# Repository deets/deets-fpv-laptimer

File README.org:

| Pin | Function |
|-----+----------|
|   1 | data     |
|   2 | cs       |
|   3 | clk      |
|   4 | gnd      |
|   5 | vcc      |
|   6 | rssi     |
|   7 | ?        |
|   8 | video    |
|   9 | gnd      |

* Credits

https://github.com/Spacefish/RichWave/blob/master/RichWave.cpp

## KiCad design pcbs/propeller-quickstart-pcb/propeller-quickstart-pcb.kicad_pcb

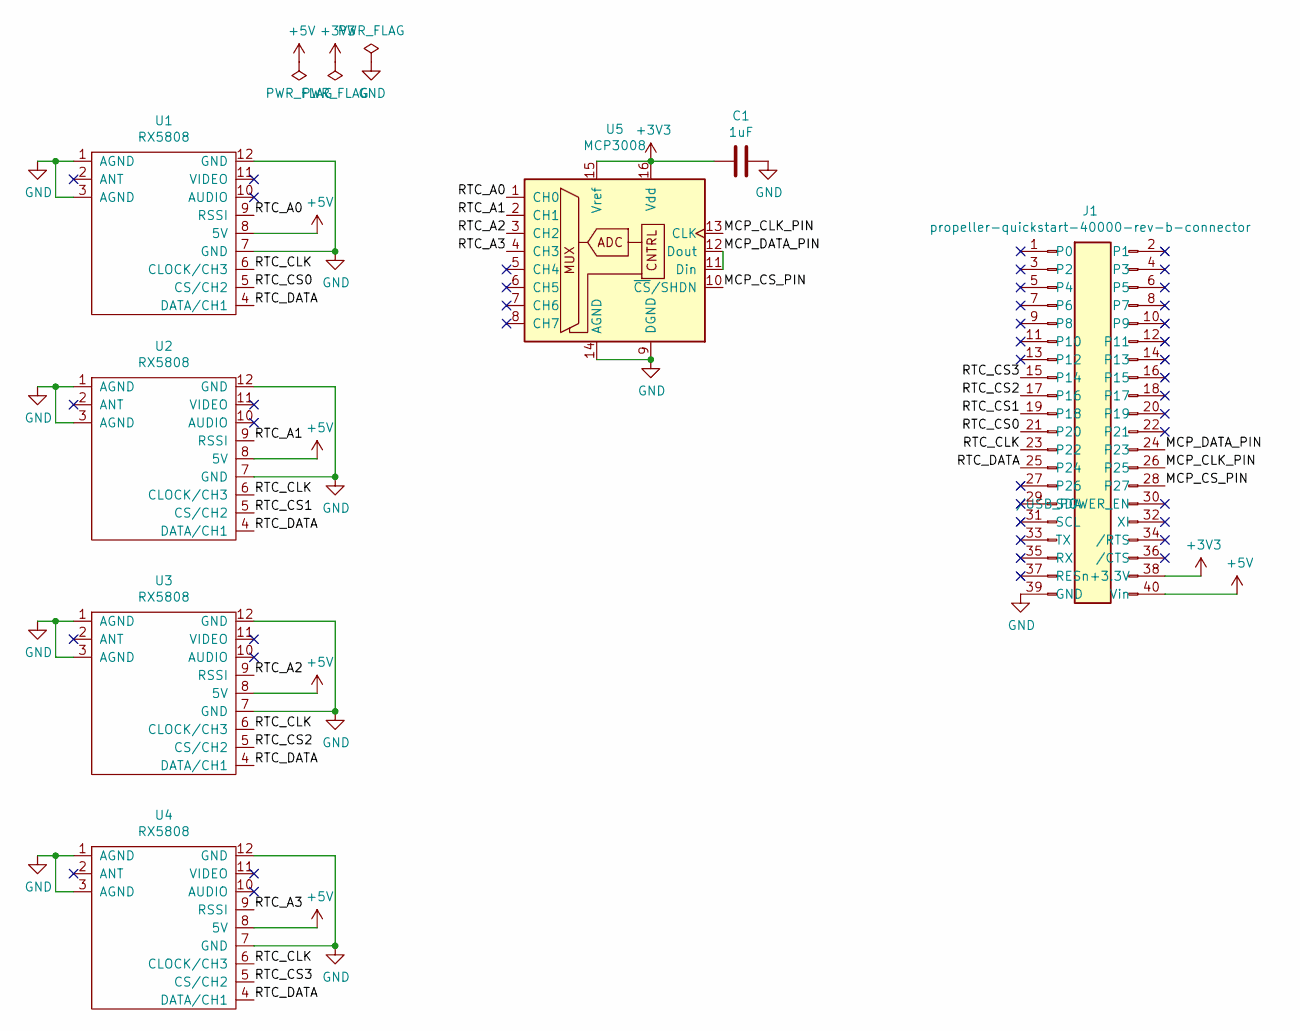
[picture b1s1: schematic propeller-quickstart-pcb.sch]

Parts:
C1: 1uF; C_Radial_D5.0mm_H5.0mm_P2.00mm
J1: propeller-quickstart-40000-rev-b-connector; PinHeader_2x20_P2.54mm_Vertical
U1, U2, U3, U4: RX5808
U5: MCP3008; DIP-16_W7.62mm

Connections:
+3V3: C1.2, J1.38 (+3.3V), U5.15 (Vref), U5.16 (Vdd)
+5V: J1.40 (Vin), U1.8 (5V), U2.8 (5V), U3.8 (5V), U4.8 (5V)
/MCP_CLK_PIN: J1.26 (P25), U5.13 (CLK)
/MCP_CS_PIN: J1.28 (P27), U5.10 (~CS~/SHDN)
/MCP_DATA_PIN: J1.24 (P23), U5.11 (Din), U5.12 (Dout)
/RTC_A0: U1.9 (RSSI), U5.1 (CH0)
/RTC_A1: U2.9 (RSSI), U5.2 (CH1)
/RTC_A2: U3.9 (RSSI), U5.3 (CH2)
/RTC_A3: U4.9 (RSSI), U5.4 (CH3)
/RTC_CLK: J1.23 (P22), U1.6 (CLOCK/CH3), U2.6 (CLOCK/CH3), U3.6 (CLOCK/CH3), U4.6 (CLOCK/CH3)
/RTC_CS0: J1.21 (P20), U1.5 (CS/CH2)
/RTC_CS1: J1.19 (P18), U2.5 (CS/CH2)
/RTC_CS2: J1.17 (P16), U3.5 (CS/CH2)
/RTC_CS3: J1.15 (P14), U4.5 (CS/CH2)
/RTC_DATA: J1.25 (P24), U1.4 (DATA/CH1), U2.4 (DATA/CH1), U3.4 (DATA/CH1), U4.4 (DATA/CH1)
GND: C1.1, J1.39 (GND), U1.1 (AGND), U1.3 (AGND), U1.7 (GND), U1.12 (GND), U2.1 (AGND), U2.3 (AGND), U2.7 (GND), U2.12 (GND), U3.1 (AGND), U3.3 (AGND), U3.7 (GND), U3.12 (GND), U4.1 (AGND), U4.3 (AGND), U4.7 (GND), U4.12 (GND), U5.9 (DGND), U5.14 (AGND)

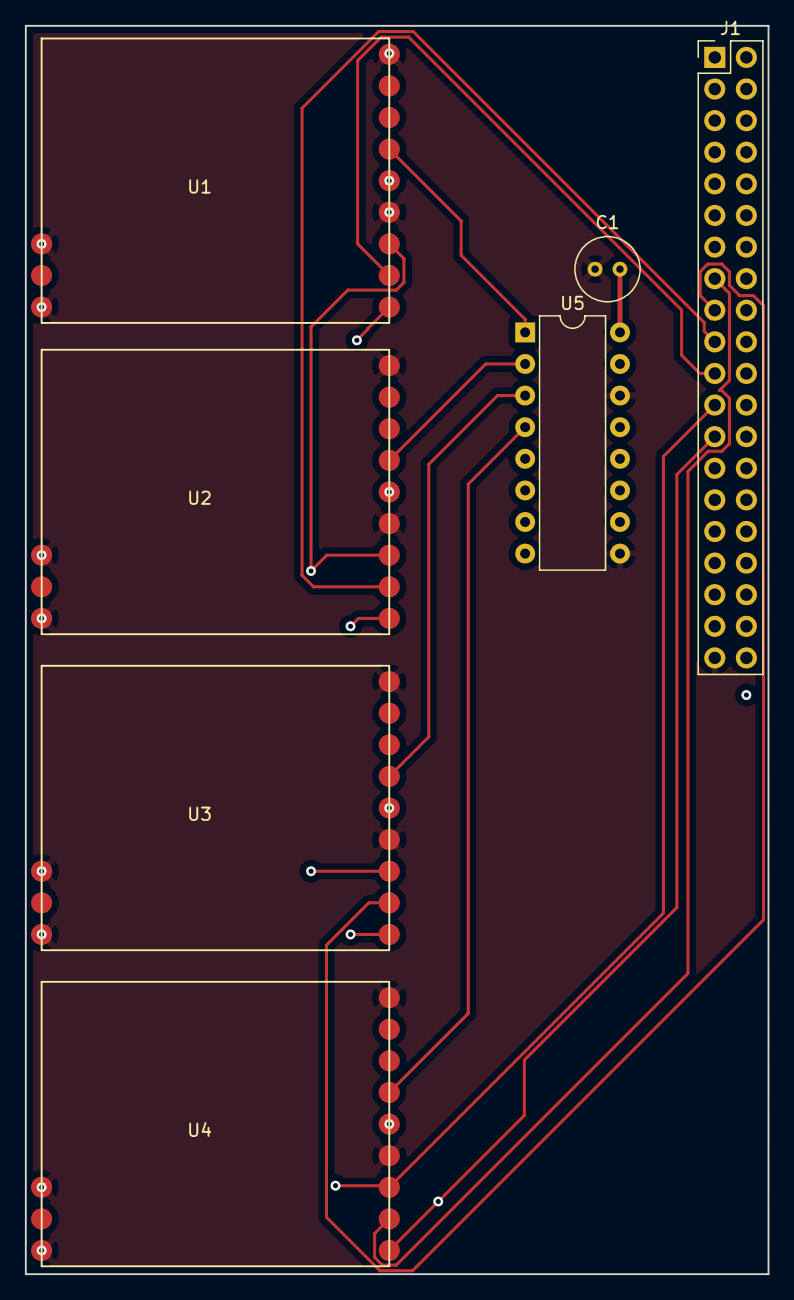
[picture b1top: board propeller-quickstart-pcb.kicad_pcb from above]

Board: 4 copper layers, 59.7 x 100.3 mm, 7 parts (0 on the bottom side), 16 nets.

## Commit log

2018-10-27 Working channel selection in SPIN
2018-10-28 Remove superflous state
2018-10-28 Cleanup and rename
2018-10-28 Add serial communication to the mix
2018-10-28 First stab at reading in data
2018-10-28 Scanner moder and visualisation works
2018-10-28 Now visualisation with channel-names
2018-10-28 Fixed range
2018-11-01 Add more datasheets
2018-11-01 Compile in emacs
2018-12-08 Add aomway channels and improve output
2018-12-08 Start implementing mcp3008 in assembly
2018-12-08 Add a few datasheets
2020-01-04 Add OpenEmbedded based minimal linux
2020-01-04 Restarted work on this
2020-01-04 Introduce execution modes, currently simply switched by incoming bytes
2020-01-04 Adapt scanner visualisation to current setup
2020-01-04 remove old implementations
2020-01-04 Show time deltas
2020-01-04 Enhance output of (c)onfiguration command
2020-01-04 Implement laptimer mode on controller plus visualisation
    Turns out 115200 is a stable data-rate. Higher would eat too many
    tuning commands
2020-01-04 Introduce configurable count of RTCs
2020-01-04 Simplify mpc setup
2020-01-04 Add second VRX and adapt protocol
2020-01-04 Begin tornado server
2020-01-04 Slice off a few redundant bytes
2020-01-04 Introduce flash command
2020-01-04 Start moving code into the package
2020-01-04 Remove cruft
2020-01-05 Introduce SQLAlchemy and py.test testing the model
2020-01-05 Fleshing out the db model
2020-01-05 Add DB to tornado server
2020-01-05 Add commandline recording tool
2020-01-05 Reduce laptime output even further
2020-01-05 Begin breakout PCB for four RTCs
2020-01-05 Change RTC_CS pin assignment to conform with new PCB layout
2020-01-05 Introduce a pause command
    The visualisation needs this because otherwise it will desync.
    The reason is probably a buffer overrun in the linux serial driver
2020-01-06 First version of the PCB
2020-02-01 Remove one RTC because of refactoring for I2C
2020-02-02 Begin work on RH compatibility layer via I2C
2020-02-03 Super basic node api level identification works
2020-02-03 Added more commands (set/get frequency, set/get enter/exit levels)
2020-02-03 First stab at changing frequency and returing rssi
2020-02-08 Migrate serial to channel-interface
2020-02-08 Add ADC spread calc script
2020-02-08 Some minor refinements, still not really happy with the mapping
2020-02-08 Introduce simple one-pole filter with fixed point arithmetic
2020-02-08 Rudimentary lap tracking
2020-02-09 Introduce fake mcp3008 to work with RotorHazard under controlled circumstances
2020-02-09 Add I2C and fake mcp button
2020-03-22 Start working on SPI version
2020-03-22 Add two lines to allow for SPI
2020-03-22 wip: communicate lowest bit of cnt
2020-03-24 bit-counting works. which is profoundly weird
2020-03-24 shift out cnt MSB first
    MSB first as the PI can't be configured to do LSB first
    Also adapt to mode 0
2020-03-24 Shift out what came in last
2020-03-25 Little self modifying code example
2020-03-27 Writing the full 9 words works
2020-03-28 Looks as if the size/wraparound computation now is correct
2020-03-28 Fix bug in read position calculation
2021-03-19 Bump pillow from 7.0.0 to 8.1.1
    Bumps [pillow](https://github.com/python-pillow/Pillow) from 7.0.0 to 8.1.1.
    - [Release notes](https://github.com/python-pillow/Pillow/releases)
    - [Changelog](https://github.com/python-pillow/Pillow/blob/master/CHANGES.rst)
    - [Commits](https://github.com/python-pillow/Pillow/compare/7.0.0...8.1.1)
2021-03-20 Bump jinja2 from 2.10.3 to 2.11.3
    Bumps [jinja2](https://github.com/pallets/jinja) from 2.10.3 to 2.11.3.
    - [Release notes](https://github.com/pallets/jinja/releases)
    - [Changelog](https://github.com/pallets/jinja/blob/master/CHANGES.rst)
    - [Commits](https://github.com/pallets/jinja/compare/2.10.3...2.11.3)
2021-06-08 Bump pillow from 8.1.2 to 8.2.0
    Bumps [pillow](https://github.com/python-pillow/Pillow) from 8.1.2 to 8.2.0.
    - [Release notes](https://github.com/python-pillow/Pillow/releases)
    - [Changelog](https://github.com/python-pillow/Pillow/blob/master/CHANGES.rst)
    - [Commits](https://github.com/python-pillow/Pillow/compare/8.1.2...8.2.0)
    ---
    updated-dependencies:
2021-09-08 Bump pillow from 8.1.2 to 8.3.2
    Bumps [pillow](https://github.com/python-pillow/Pillow) from 8.1.2 to 8.3.2.
    - [Release notes](https://github.com/python-pillow/Pillow/releases)
    - [Changelog](https://github.com/python-pillow/Pillow/blob/master/CHANGES.rst)
    - [Commits](https://github.com/python-pillow/Pillow/compare/8.1.2...8.3.2)
    ---
    updated-dependencies:
2022-01-13 Bump pillow from 8.1.2 to 9.0.0
    Bumps [pillow](https://github.com/python-pillow/Pillow) from 8.1.2 to 9.0.0.
    - [Release notes](https://github.com/python-pillow/Pillow/releases)
    - [Changelog](https://github.com/python-pillow/Pillow/blob/main/CHANGES.rst)
    - [Commits](https://github.com/python-pillow/Pillow/compare/8.1.2...9.0.0)
    ---
    updated-dependencies:
2022-01-21 Bump ipython from 7.11.1 to 7.16.3
    Bumps [ipython](https://github.com/ipython/ipython) from 7.11.1 to 7.16.3.
    - [Release notes](https://github.com/ipython/ipython/releases)
    - [Commits](https://github.com/ipython/ipython/compare/7.11.1...7.16.3)
    ---
    updated-dependencies:
    - dependency-name: ipython
2022-03-12 Bump pillow from 9.0.0 to 9.0.1
    Bumps [pillow](https://github.com/python-pillow/Pillow) from 9.0.0 to 9.0.1.
    - [Release notes](https://github.com/python-pillow/Pillow/releases)
    - [Changelog](https://github.com/python-pillow/Pillow/blob/main/CHANGES.rst)
    - [Commits](https://github.com/python-pillow/Pillow/compare/9.0.0...9.0.1)
    ---
    updated-dependencies:
2022-11-22 Bump pillow from 9.0.0 to 9.3.0
    Bumps [pillow](https://github.com/python-pillow/Pillow) from 9.0.0 to 9.3.0.
    - [Release notes](https://github.com/python-pillow/Pillow/releases)
    - [Changelog](https://github.com/python-pillow/Pillow/blob/main/CHANGES.rst)
    - [Commits](https://github.com/python-pillow/Pillow/compare/9.0.0...9.3.0)
    ---
    updated-dependencies:
2022-12-27 Bump setuptools from 60.5.0 to 65.5.1
    Bumps [setuptools](https://github.com/pypa/setuptools) from 60.5.0 to 65.5.1.
    - [Release notes](https://github.com/pypa/setuptools/releases)
    - [Changelog](https://github.com/pypa/setuptools/blob/main/CHANGES.rst)
    - [Commits](https://github.com/pypa/setuptools/compare/v60.5.0...v65.5.1)
    ---
    updated-dependencies:
